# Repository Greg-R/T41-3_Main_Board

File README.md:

The documentation for this module is located here:

<https://kf5n.com/t41-3_hardware/main/>

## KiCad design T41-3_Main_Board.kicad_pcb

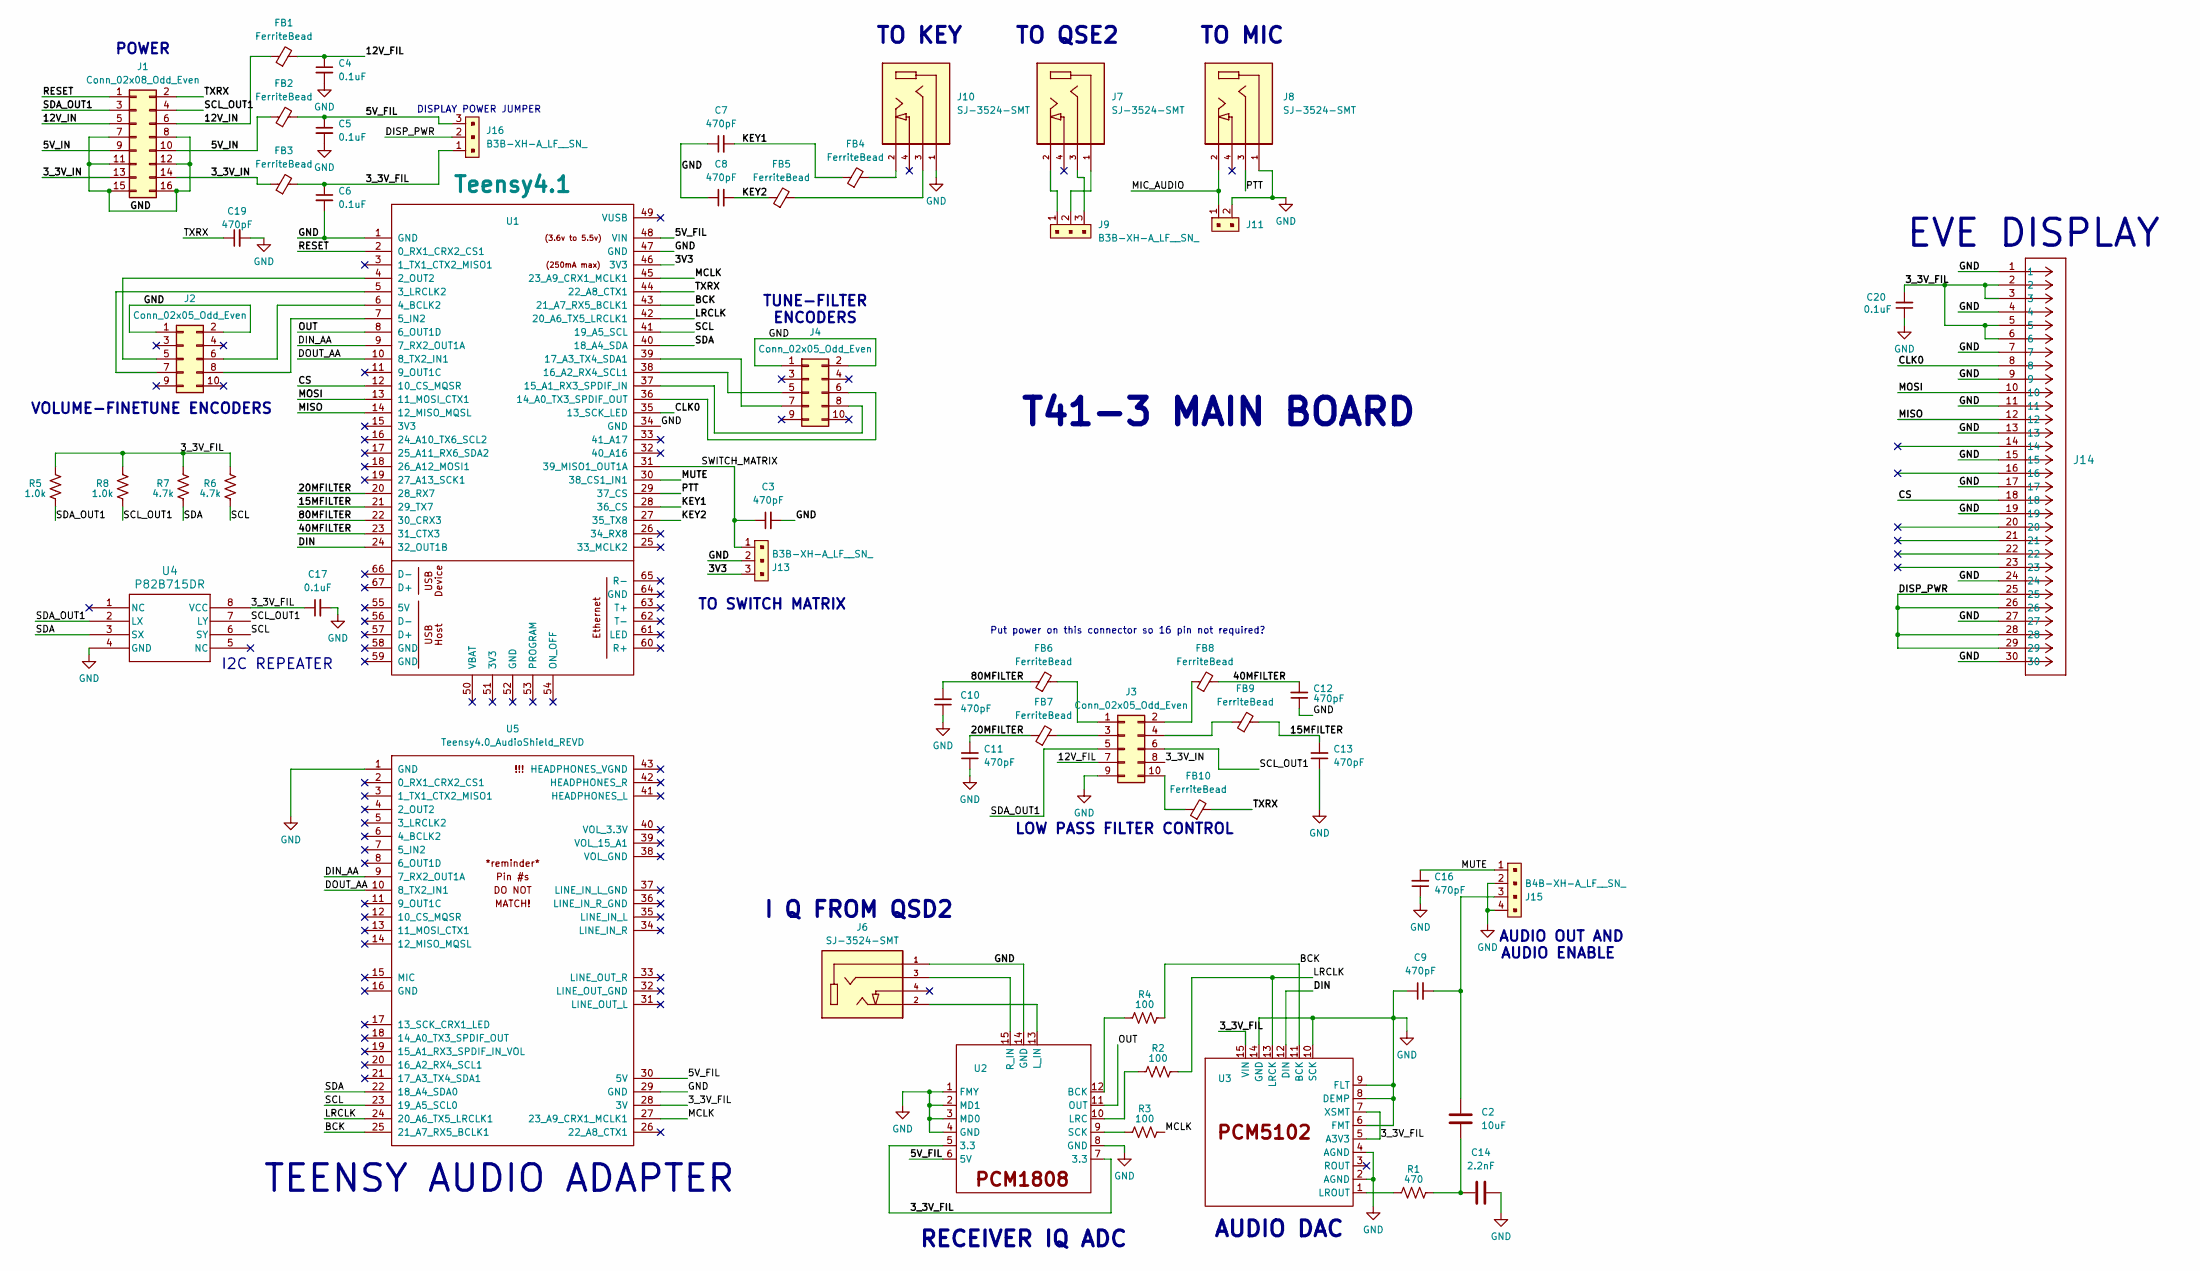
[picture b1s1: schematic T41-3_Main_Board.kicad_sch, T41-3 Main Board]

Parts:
C2: 10uF; C_1206_3216Metric
C3, C7, C8, C9, C10, C11, C12, C13, C16, C19: 470pF; C_1206_3216Metric
C4, C5, C6, C17, C20: 0.1uF; C_1206_3216Metric
C14: 2.2nF; C_1206_3216Metric
FB1, FB2, FB3, FB4, FB5, FB6, FB7, FB8, FB9, FB10: FerriteBead; L_1206_3216Metric
J1: Conn_02x08_Odd_Even; IDC-Header_2x08_P2.54mm_Vertical
J2, J3, J4: Conn_02x05_Odd_Even; IDC-Header_2x05_P2.54mm_Vertical
J6, J7, J8, J10: SJ-3524-SMT; CUI_SJ-3524-SMT; PARTREV 1.03
J9, J13, J16: B3B-XH-A_LF__SN_; PinHeader_1x3_P2.5mm_Drill1.1mm; MPN B3B-XH-A(LF)(SN); Digi-Key_PN 455-2248-ND
J11: B2B-XH-A_LF__SN_; PinHeader_1x2_P2.5mm_Drill1.1mm; MPN B2B-XH-A(LF)(SN); Digi-Key_PN 455-2247-ND
J14: 5019513030; 5019513030_30_pin
J15: B4B-XH-A_LF__SN_; PinHeader_1x4_P2.5mm_Drill1.1mm; MPN B4B-XH-A(LF)(SN); Digi-Key_PN 455-2249-ND
R1: 470; R_1206_3216Metric
R2, R3, R4: 100; R_1206_3216Metric
R5, R8: 1.0k; R_1206_3216Metric
R6, R7: 4.7k; R_1206_3216Metric
U1: Teensy4.1; Teensy41
U2: PCM1808_module
U3: PCM5102_module
U4: P82B715DR; SOIC-8_3.9x4.9mm_P1.27mm
U5: Teensy4.0_AudioShield_REVD; 4.0audioshield

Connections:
/3V3: J13.3, U1.46 (3V3)
/3_3V_FIL: C6.1, C17.1, C20.2, FB3.2, J14.2, J14.3, J14.5, J14.6, J16.1, R5.2, R6.2, R7.2, R8.2, U2.5 (3.3), U2.7 (3.3), U3.5 (A3V3), U3.7 (XSMT), U3.15 (VIN), U4.8 (VCC), U5.28 (3V)
/3_3V_IN: FB3.1, J1.13, J1.14, J3.8
/5V_FIL: C5.1, FB2.2, J16.3, U1.48 (VIN), U2.6 (5V), U5.30 (5V)
/5V_IN: FB2.1, J1.9, J1.10
/12V_FIL: C4.1, FB1.2, J3.7
/12V_IN: FB1.1, J1.5, J1.6
/15MFILTER: C13.2, FB9.2, U1.21 (29_TX7)
/20MFILTER: C11.2, FB7.1, U1.20 (28_RX7)
/40MFILTER: C12.2, FB8.2, U1.23 (31_CTX3)
/80MFILTER: C10.2, FB6.1, U1.22 (30_CRX3)
/BCK: R4.2, U1.43 (21_A7_RX5_BCLK1), U3.11 (BCK), U5.25 (21_A7_RX5_BCLK1)
/CLK0: J14.8, U1.35 (13_SCK_LED)
/CS: J14.18, U1.12 (10_CS_MQSR)
/DIN: U1.24 (32_OUT1B), U3.12 (DIN)
/DIN_AA: U1.9 (7_RX2_OUT1A), U5.9 (7_RX2_OUT1A)
/DISP_PWR: J14.25, J14.26, J14.28, J14.29, J16.2
/DOUT_AA: U1.10 (8_TX2_IN1), U5.10 (8_TX2_IN1)
/KEY1: C7.2, FB4.1, U1.28 (36_CS)
/KEY2: C8.2, FB5.1, U1.27 (35_TX8)
/LRCLK: R2.2, U1.42 (20_A6_TX5_LRCLK1), U3.13 (LRCK), U5.24 (20_A6_TX5_LRCLK1)
/MCLK: R3.2, U1.45 (23_A9_CRX1_MCLK1), U5.27 (23_A9_CRX1_MCLK1)
/MIC_AUDIO: J8.2, J11.1
/MISO: J14.12, U1.14 (12_MISO_MQSL)
/MOSI: J14.10, U1.13 (11_MOSI_CTX1)
/MUTE: C16.2, J15.1, U1.30 (38_CS1_IN1)
/OUT: U1.8 (6_OUT1D), U2.11 (OUT)
/PTT: J8.3, U1.29 (37_CS)
/RESET: J1.1, U1.2 (0_RX1_CRX2_CS1)
/SCL: R6.1, U1.41 (19_A5_SCL), U4.6 (SY), U5.23 (19_A5_SCL0)
/SCL_OUT1: J1.4, J3.6, R8.1, U4.7 (LY)
/SDA: R7.1, U1.40 (18_A4_SDA), U4.3 (SX), U5.22 (18_A4_SDA0)
/SDA_OUT1: J1.3, J3.5, R5.1, U4.2 (LX)
/SWITCH_MATRIX: C3.1, J13.1, U1.31 (39_MISO1_OUT1A)
/TXRX: C19.1, FB10.2, J1.2, U1.44 (22_A8_CTX1)
GND: C3.2, C4.2, C5.2, C6.2, C7.1, C8.1, C9.1, C10.1, C11.1, C12.1, C13.1, C14.1, C16.1, C17.2, C19.2, C20.1, J1.7, J1.8, J1.11, J1.12, J1.15, J1.16, J2.1, J2.2, J3.9, J4.1, J4.2, J6.1, J8.1, J10.1, J11.2, J13.2, J14.1, J14.4, J14.7, J14.9, J14.11, J14.13, J14.15, J14.17, J14.19, J14.24, J14.27, J14.30, J15.2, J15.4, U1.1 (GND), U1.34 (GND), U1.47 (GND), U2.1 (FMY), U2.2 (MD1), U2.3 (MD0), U2.4 (GND), U2.8 (GND), U2.14 (GND), U3.2 (AGND), U3.4 (AGND), U3.6 (FMT), U3.8 (DEMP), U3.9 (FLT), U3.10 (SCK), U3.14 (GND), U4.4 (GND), U5.1 (GND), U5.29 (GND)
unnamed: C2.2, C9.2, J15.3
unnamed: C2.1, C14.2, R1.2
unnamed: FB4.2, J10.2
unnamed: FB5.2, J10.3
unnamed: J2.5, U1.4 (2_OUT2)
unnamed: J2.6, U1.6 (4_BCLK2)
unnamed: J2.7, U1.5 (3_LRCLK2)
unnamed: J2.8, U1.7 (5_IN2)
unnamed: FB6.2, J3.1
unnamed: FB8.1, J3.2
unnamed: FB7.2, J3.3
unnamed: FB9.1, J3.4
unnamed: FB10.1, J3.10
unnamed: J4.5, U1.38 (16_A2_RX4_SCL1)
unnamed: J4.6, U1.36 (14_A0_TX3_SPDIF_OUT)
unnamed: J4.7, U1.39 (17_A3_TX4_SDA1)
unnamed: J4.8, U1.37 (15_A1_RX3_SPDIF_IN)
unnamed: J7.1, J9.2
unnamed: J7.2, J9.1
unnamed: J7.3, J9.3
unnamed: R4.1, U2.12 (BCK)
unnamed: R2.1, U2.10 (LRC)
unnamed: J6.2, U2.13 (L_IN)
unnamed: J6.3, U2.15 (R_IN)
unnamed: R3.1, U2.9 (SCK)
unnamed: R1.1, U3.1 (LROUT)

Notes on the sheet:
TO QSE2
ENCODERS
TO SWITCH MATRIX
VOLUME-FINETUNE
I2C REPEATER
TO MIC
AUDIO OUT AND
I Q FROM QSD2
TUNE-FILTER
DISPLAY POWER JUMPER
RECEIVER IQ ADC
TO KEY
AUDIO ENABLE
T41-3 MAIN BOARD
Put power on this connector so 16 pin not required?
EVE DISPLAY
AUDIO DAC
POWER
TEENSY AUDIO ADAPTER
LOW PASS FILTER CONTROL

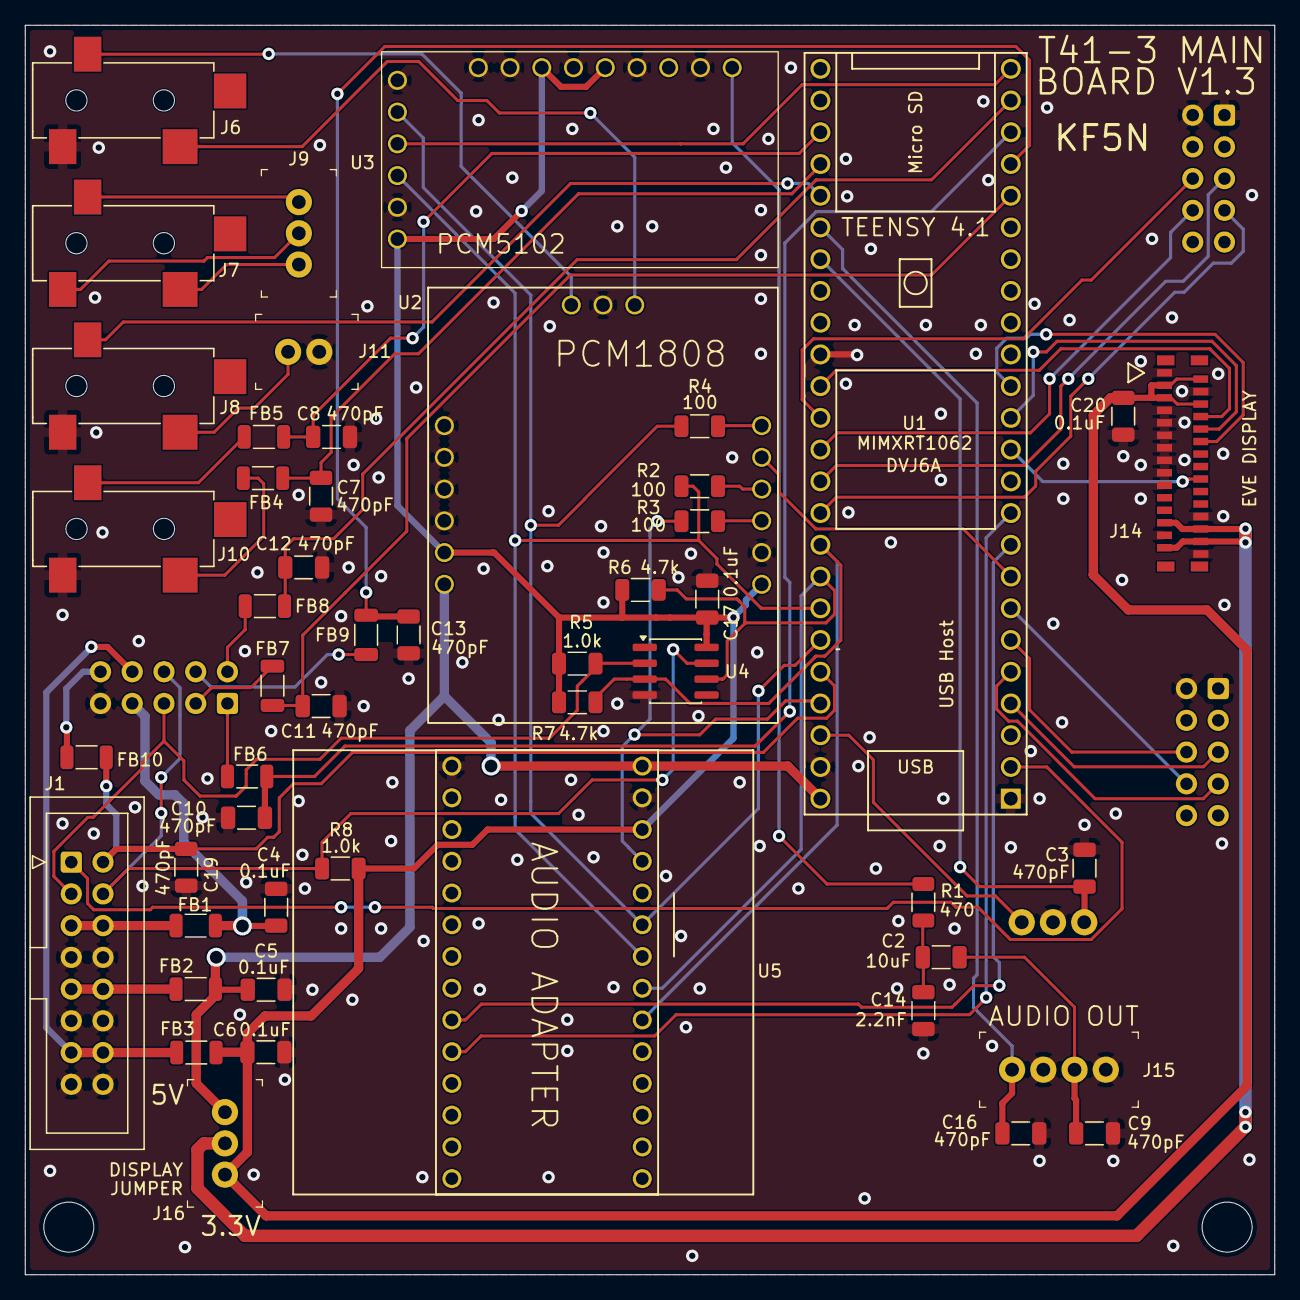
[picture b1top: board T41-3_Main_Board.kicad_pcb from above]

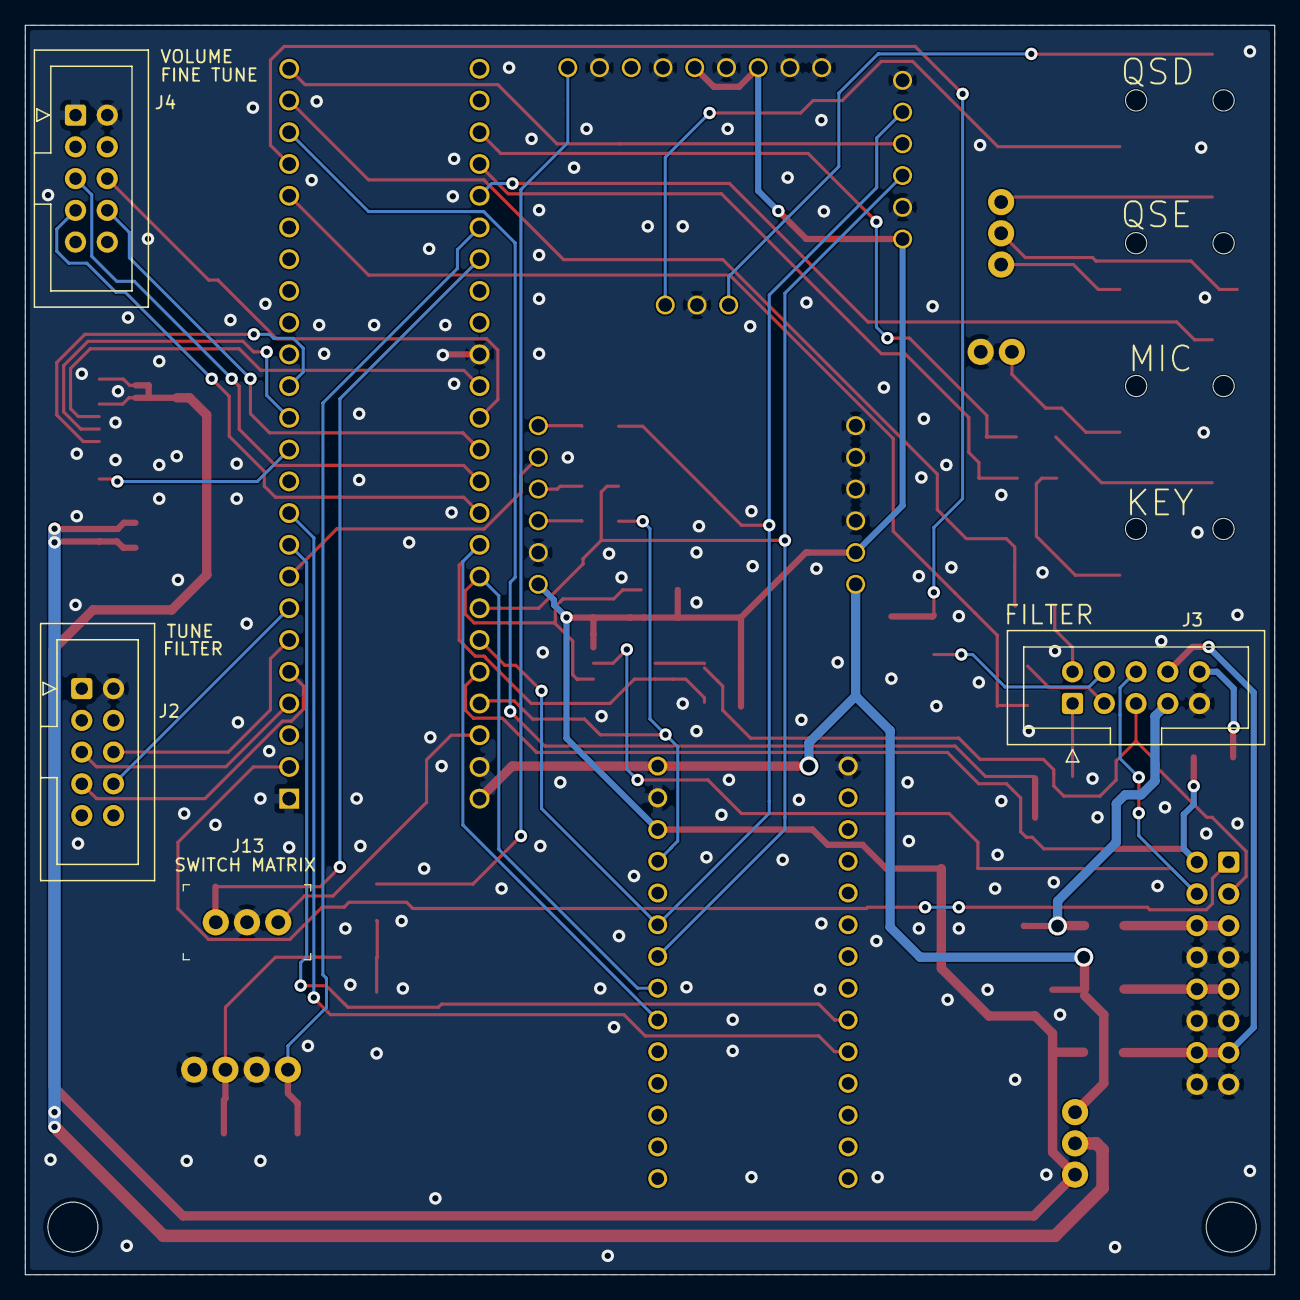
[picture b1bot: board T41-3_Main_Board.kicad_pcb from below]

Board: 2 copper layers, 100.0 x 100.0 mm, 54 parts (4 on the bottom side), 62 nets.
